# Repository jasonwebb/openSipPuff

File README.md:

# openSip+Puff

__openSip+Puff__ aims to provide a cheap, simple, open, and modern alternative input method based on the breath of a user that can be easily mapped to a variety of common actions like mouse clicks and keypresses.

The ultimate goal of this project is to go beyond simple utilitarian functionality and provide a new modality for creative expression that is meaningful for people with or without limited mobility. For me this means musical expression and visual art applications, but you are welcome to take it in whatever direction you want!

In contrast to other DIY sip-and-puff solutions, this project aims to keep the number of parts and assembly steps to a minimum while keeping the focus entirely on the digitization of breath - nothing more, nothing less. The hope is that this device can be manufactured as a true "plug-and-play", standalone device such that the only remaining steps that users will need to complete on their own are to (1) pop the board into an enclosure, (2) attach a mouthpiece with tubing, and (3) plug in a USB cable. With the help of native USB HID functionality, this device should (theoretically) be as easy to set up as any keyboard or mouse - no special drivers needed!

In keeping the focus tight and the parts count low it is expected that this device will be possible to sell for under $100 (ideally around $60). Fewer external parts also means fewer points of failure, so the device should last a while with minimal need for maintenance.

## Features
### Hardware
* ATmega32u4 microcontroller running the [Arduino Leonardo bootloader](https://www.arduino.cc/en/Main/ArduinoBoardLeonardo), allowing for the device to work as a standard USB HID device (mouse, keyboard, MIDI, etc) without any special drivers.
* [MPXV7007GP](https://www.digikey.com/product-detail/en/nxp-usa-inc/MPXV7007GP/MPXV7007GP-ND/1168441) analog pressure sensor for detecting direction and strength of sips and puffs.
* USB mini-B port so it can be connected to any PC
* 4-pin I2C interface for future expansion (may be removed if a good use case isn't identified)

### Firmware
```
TODO:
=====
  1. Sips and puffs need to be associated with actions (keypresses, mouse clicks, MIDI notes, etc) using some 
     sort of persistent data structure that can be loaded from EEPROM when the device is powered on.
  2. Patterns of sips and puffs should also be supported at some point. For example, one puff for left mouse 
     click, two puffs for right mouse click.
  3. Output raw analog values as serial data over USB to be transformed into other interesting actions by custom 
     applications or something like Wekinator.
  4. Output analog data as MIDI CC changes so the device can be used for expressive musical applications.
```

### Software
```
TODO:
=====
To make it easy for non-technical users to reconfigure the device, some sort of easy-to-use desktop application 
should be built. 

Once the firmware is worked out, I'd like to experiment with using Electron and modern web technologies to build 
this interface. 
```

### Mechanical
```
TODO:
=====
Connecting a plain plastic tube directly the sensor is fine for prototyping, but is not hygienic for real-world 
users. Some sort of easy-to-replace filter(s) should be added to capture saliva and particulates before they 
reach the sensor. 

I don't know much about these sorts of filters, so if you have some experience or ideas please send them to me!
```

## Similar projects
When I started building this project there weren't any other viable DIY sip-and-puff interfaces out there, but in the past year so a few great projects have sprung up that are worth looking at!

* [LipSync](https://github.com/makersmakingchange/LipSync) - uses an Arduino Pro Micro board and the [MPXV7002DPT1](https://www.digikey.com/product-detail/en/nxp-usa-inc/MPXV7002DPT1/MPXV7002DPT1CT-ND/3524215) sensor, as well as an optional Bluetooth breakout board. Includes a custom mouth-operated joystick built using 3D-printed parts and FSRs, all housed in a 3D-printed enclosure. _Incredible_ documentation, and available as a kit or fully assembled through [Makers Making Change](https://www.makersmakingchange.com/project/lipsync/).
* [FLipMouse](https://github.com/asterics/FLipMouse) - uses a Teensy LC and the [MPXV7007GP](https://www.digikey.com/product-detail/en/nxp-usa-inc/MPXV7007GP/MPXV7007GP-ND/1168441) sensor. Includes a custom mouth-operated joystick that is nearly identical to LipSync, all housed in a laser-cut acrylic enclosure. Available as a kit through [Hackerspace Shop](https://hackerspaceshop.com/products/flipmouse-diy-kit).
* [The 'Sup](https://www.instructables.com/id/The-Sup-a-Mouse-for-Quadriplegics-Low-Cost-and-Ope/) - uses an Arduino Pro Micro and a [MPXV7002DP](https://www.ebay.com/itm/MD-PS002-MPXV7002DP-Transducer-Pressure-Sensor-Differential-Breakout-Board-/401602810835?oid=202106155765) sensor on a breakout board, as well as an off-the-shelf [two-axis joystick module](https://www.ebay.com/itm/Module-PS2-Lever-Hots-Two-axis-Sensor-Joystick-Game-Controller/302615277464?hash=item467546af98:g:eGQAAOSwKXdaadFS). Features a unique 3D-printed mouthpiece that couples the joystick and tubing, though no filters are used.

## License
This work is licensed under a [Creative Commons Attribution-NonCommercial-ShareAlike 4.0 International License](http://creativecommons.org/licenses/by-nc-sa/4.0/).

Use this project to learn, tinker and share with friends. You are completely free to build this project for individuals  who need it. Small commercial runs for workshops or other educational uses are also completely cool.

The only reason that a fully-permissive open-source license is not used is to discourage, however naively, abuse through mass production and sale of this project by companies who are not as passionate about the quality and core mission of the project. If you're interested in producing and distributing this project to larger markets, please contact me and maybe we can collaborate!

## Media

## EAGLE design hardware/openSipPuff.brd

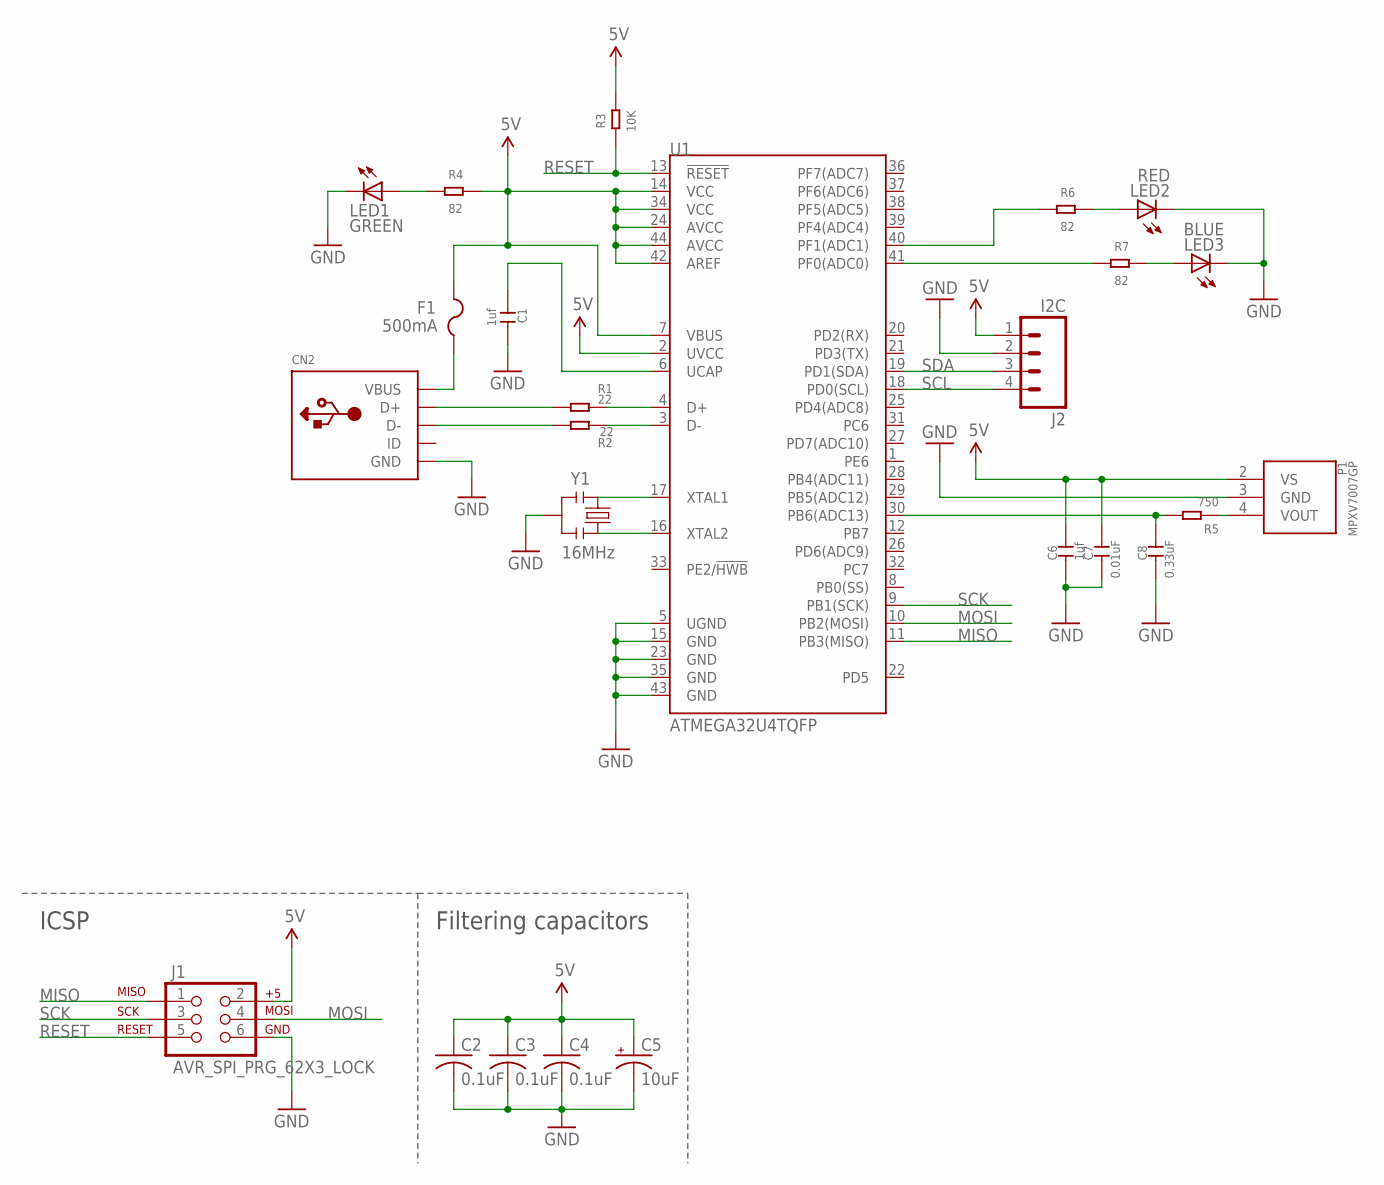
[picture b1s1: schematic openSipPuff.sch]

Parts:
C1, C6: 1uf; C0805
C2, C3, C4: 0.1uF; C0805K
C5: 10uF; A/3216-18R
C7: 0.01uF; C0805
C8: 0.33uF; C0805
CN2: USBMINIB; USB-MINIB
F1: 500mA; R1206
J1: AVR_SPI_PRG_62X3_LOCK; 2X3_LOCK
J2: I2C; 1X04
LED1: GREEN; CHIPLED_0805
LED2: RED; CHIPLED_0805
LED3: BLUE; CHIPLED_0805
P1: MPXV7007GP; SOP8
R1, R2: 22; R0805
R3: 10K; R0805
R4, R6, R7: 82; R0805
R5: 750; R0805
U1: ATMEGA32U4TQFP; SPARKFUN-DIGITALIC_TQFP44
Y1: 16MHz; RESONATOR-SMD

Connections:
5V: C2.1, C3.1, C4.1, C5.+, C6.2, C7.2, F1.2, J1.2, J2.1, P1.2 (VS), R3.2, R4.2, U1.2 (UVCC), U1.7 (VBUS), U1.14 (VCC), U1.24 (AVCC), U1.34 (VCC), U1.42 (AREF), U1.44 (AVCC)
D+: CN2.D+, R1.1
D-: CN2.D-, R2.1
GND: C1.2, C2.2, C3.2, C4.2, C5.-, C6.1, C7.1, C8.1, CN2.GND, J1.6, J2.2, LED1.C, LED2.C, LED3.C, P1.3 (GND), U1.5 (UGND), U1.15 (GND), U1.23 (GND), U1.35 (GND), U1.43 (GND), Y1.2
MISO: J1.1, U1.11 (PB3(MISO))
MOSI: J1.4, U1.10 (PB2(MOSI))
unnamed: R1.2, U1.4 (D+)
unnamed: R2.2, U1.3 (D-)
unnamed: C1.1, U1.6 (UCAP)
unnamed: CN2.VBUS, F1.1
unnamed: U1.17 (XTAL1), Y1.1
unnamed: U1.16 (XTAL2), Y1.3
unnamed: C8.2, R5.2, U1.30 (PB6(ADC13))
unnamed: R6.1, U1.40 (PF1(ADC1))
unnamed: R7.1, U1.41 (PF0(ADC0))
unnamed: P1.4 (VOUT), R5.1
unnamed: LED1.A, R4.1
unnamed: LED3.A, R7.2
unnamed: LED2.A, R6.2
RESET: J1.5, R3.1, U1.13 (!RESET)
SCK: J1.3, U1.9 (PB1(SCK))
SCL: J2.4, U1.18 (PD0(SCL))
SDA: J2.3, U1.19 (PD1(SDA))

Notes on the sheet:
ICSP
Filtering capacitors

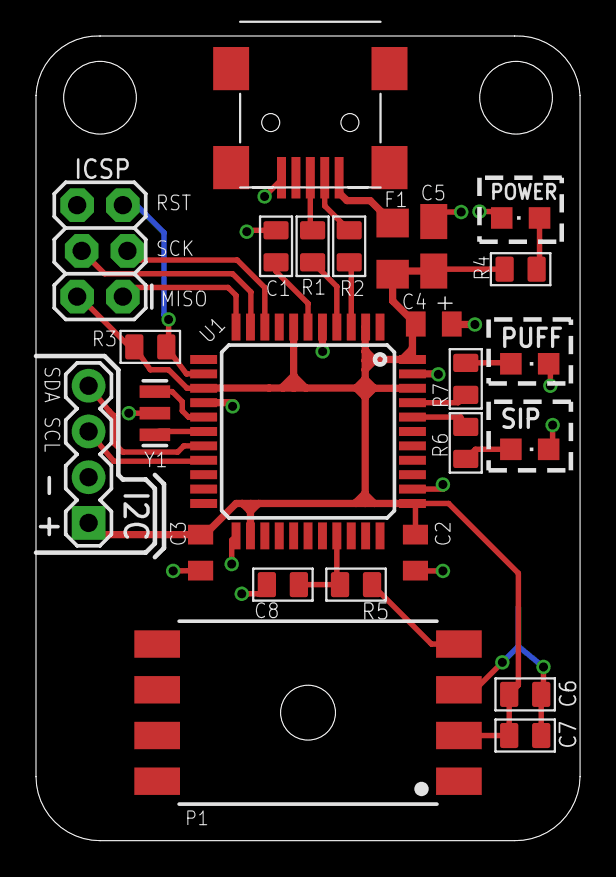
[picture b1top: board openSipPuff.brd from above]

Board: 2 copper layers, 30.2 x 44.7 mm, 25 parts (0 on the bottom side), 23 nets.

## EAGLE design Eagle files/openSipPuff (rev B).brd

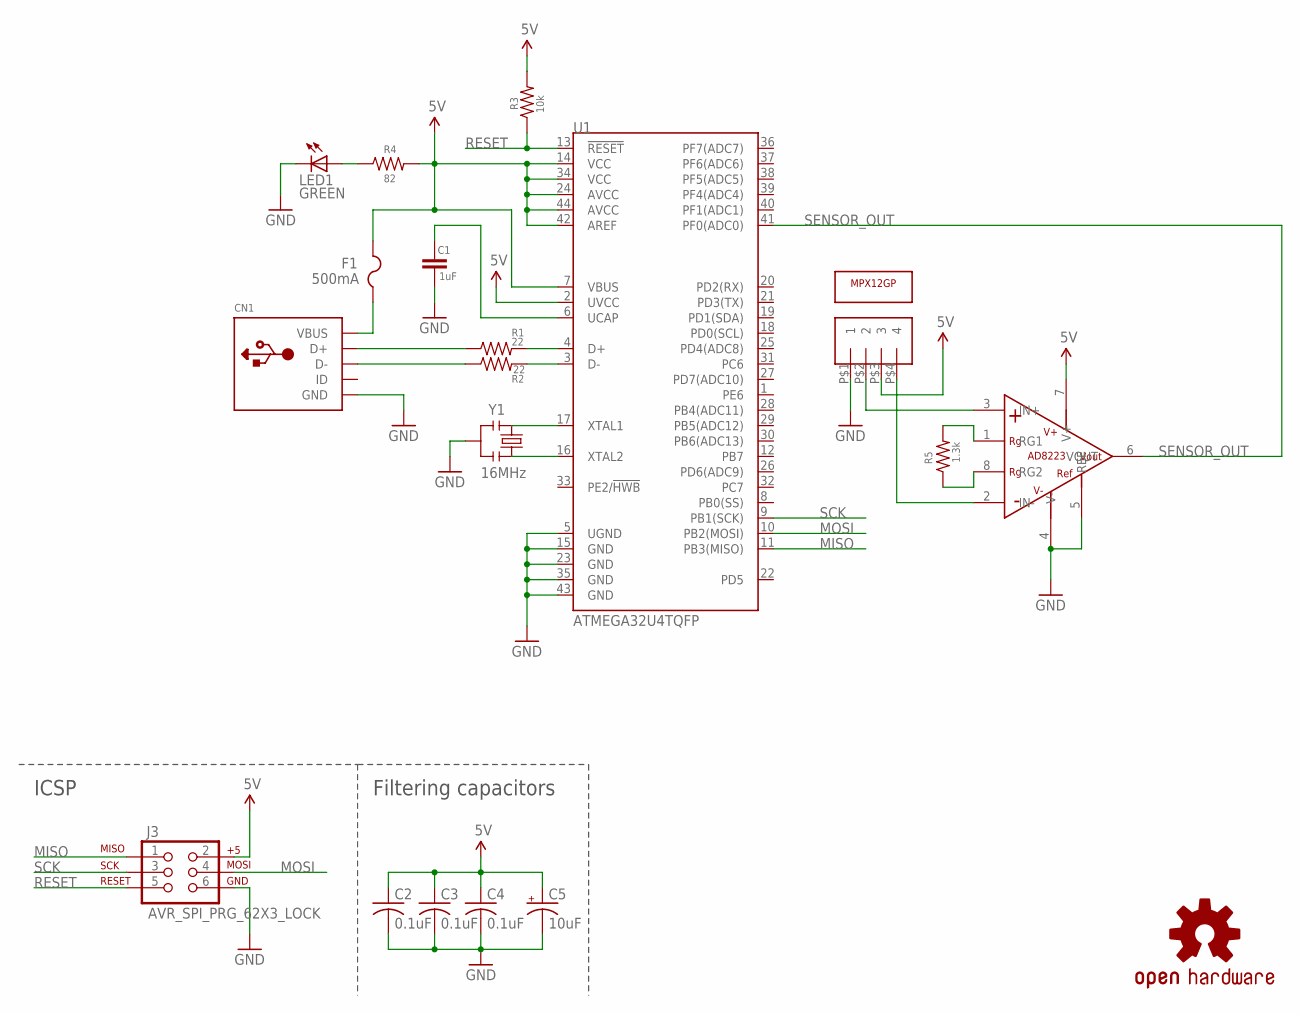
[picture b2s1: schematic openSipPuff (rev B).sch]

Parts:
C1: 1uF; 0805
C2, C3, C4: 0.1uF; C0805K
C5: 10uF; A/3216-18R
CN1: USBMOLEX; USB-MINIB-THM-MOLEX
F1: 500mA; R1206
J2: 1X04-RA
J3: AVR_SPI_PRG_62X3_LOCK; 2X3_LOCK
LED1: GREEN; CHIPLED_0805
LOGO1: OSHW-LOGOM; OSHW-LOGO-M
R1, R2: 22; 0805
R3: 10k; 0805
R4: 82; 0805
R5: 1.3k; 0805
U1: ATMEGA32U4TQFP; SPARKFUN-DIGITALIC_TQFP44
U2: AD8223; MSOP-8
U3: MPX12GP
Y1: 16MHz; RESONATOR-PTH

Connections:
5V: C2.1, C3.1, C4.1, C5.+, F1.2, J2.P$3 (3), J3.2, R3.2, R4.2, U1.2 (UVCC), U1.7 (VBUS), U1.14 (VCC), U1.24 (AVCC), U1.34 (VCC), U1.42 (AREF), U1.44 (AVCC), U2.7 (V+)
D+: CN1.D+, R1.1
D-: CN1.D-, R2.1
GND: C1.2, C2.2, C3.2, C4.2, C5.-, CN1.GND, J2.P$1 (1), J3.6, LED1.C, U1.5 (UGND), U1.15 (GND), U1.23 (GND), U1.35 (GND), U1.43 (GND), U2.4 (V-), U2.5 (REF), Y1.2
MISO: J3.1, U1.11 (PB3(MISO))
MOSI: J3.4, U1.10 (PB2(MOSI))
unnamed: R1.2, U1.4 (D+)
unnamed: R2.2, U1.3 (D-)
unnamed: C1.1, U1.6 (UCAP)
unnamed: CN1.VBUS, F1.1
unnamed: U1.17 (XTAL1), Y1.1
unnamed: U1.16 (XTAL2), Y1.3
unnamed: R5.2, U2.1 (RG1)
unnamed: J2.P$2 (2), U2.3 (IN+)
unnamed: R5.1, U2.8 (RG2)
unnamed: LED1.A, R4.1
unnamed: J2.P$4 (4), U2.2 (IN-)
RESET: J3.5, R3.1, U1.13 (!RESET)
SCK: J3.3, U1.9 (PB1(SCK))
SENSOR_OUT: U1.41 (PF0(ADC0)), U2.6 (VOUT)

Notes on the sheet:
ICSP
Filtering capacitors

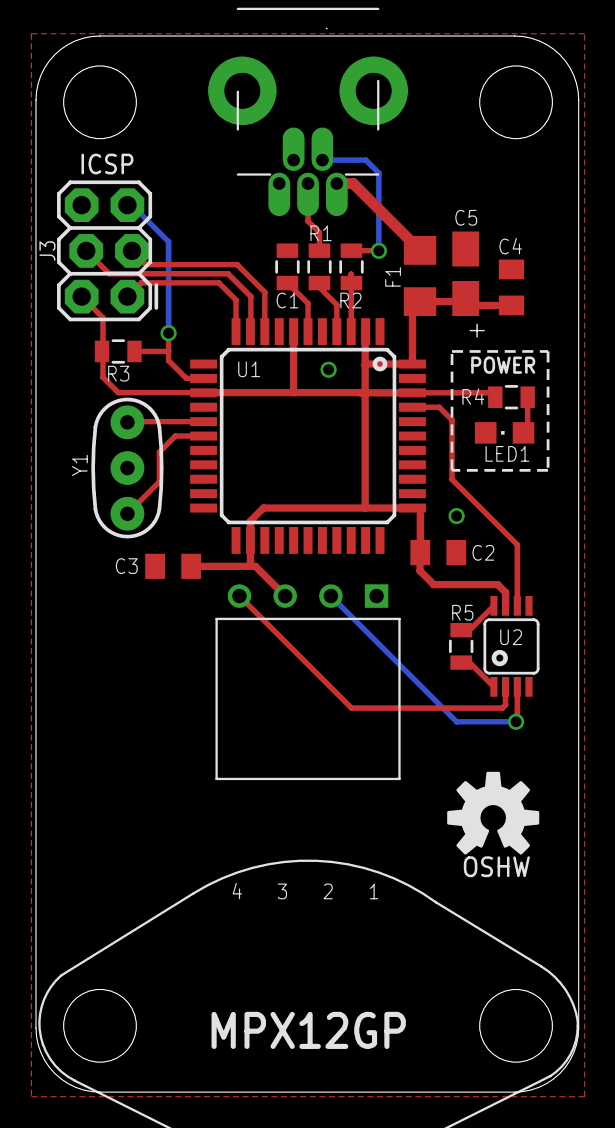
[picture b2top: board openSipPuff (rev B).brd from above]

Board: 2 copper layers, 30.1 x 58.6 mm, 20 parts (0 on the bottom side), 20 nets.

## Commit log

2013-04-15 Eagle files for Rev A and updated README
2013-04-15 Added datasheet for ATMega32u4
2013-09-26 Firmware update and rev B Eagle files
2013-09-27 Updated BOM for rev B iteration
2013-09-27 Updated 3D files with new SCAD file and STLs
2013-09-27 Added helpful SCAD includes to 3D files\lib
2014-08-28 Rev C updates
    New Eagle files and BOM.
2017-01-14 Renaming folders to be more semantic
2017-01-14 Fixing folder name case (1/2)
2017-01-14 Fixing folder names (2/2)
2017-01-14 Added latest BOM
2017-01-14 Updated BOM with CSV for web viewing
2017-01-15 Updated BOM and removed references to ambiguous rev designation.
2017-01-18 Added license to README
2017-01-19 Added README with screenshots to hardware/
2017-01-25 Updated images location and README
2018-09-13 Updating datasheets, with application notes
2018-09-13 Removing outdated enclosure files
2018-09-13 Major board updates with new sensor, I2C interface, and more
2018-09-13 Updating BOM to match latest design
2018-09-13 Moving images to dedicated folder
2018-09-13 Removing outdated BOM
2018-09-13 Updating READMEs to reference new image locations
2018-09-13 Fixing file names of board renders
2018-09-13 Adding custom library for MPXV7007GP pressure sensor
2018-09-13 Updating MPXV7007GP footprint to include hole for underside port
2019-02-17 Clarifying license in README
2019-02-17 Adding features + todos and similar projects to README
2019-02-17 Adding line breaks for readability
2019-02-20 Updating vision + other tweaks in README
2019-02-20 Adding note about Sup
2019-07-21 Update issue templates

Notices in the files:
README.md:
CC BY-NC-SA 4.0
parts and their libraries:
SparkFun-DigitalIC: Licensing: CC v3.0 Share-Alike You are welcome to use this library for commercial purposes.
